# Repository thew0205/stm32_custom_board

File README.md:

# 🛠️ Custom STM32 Development Board

This project involves the design and fabrication of a **custom STM32 development board** based on the powerful **STM32F103C8T6** ARM Cortex-M3 microcontroller.

---

## 📷 Project Images

<div align="center">

</div>

---

## 🔧 Features

This custom board was designed from scratch to expose essential microcontroller capabilities while keeping the design compact and beginner-friendly.

- ✅ **Power Supply via USB**  
  – Provides both 5V power and USB 2.0 data communication

- 🔌 **Communication Interfaces (Breakouts)**  
  – UART  
  – I2C  

- ⚡ **GPIO Pin Breakouts**  
  – Full access to STM32 GPIOs  
  – Breadboard-friendly layout

---

## 📦 Tools and Technologies Used

- **KiCad** – Schematic & PCB design
- **STM32CubeProgrammer** – Flashing and testing
- **ST-Link v2** – SWD programming and debugging

---

## 🚀 Current Progress

- ✅ First prototype designed, routed, and fabricated
- ⚠️ Encountered soldering challenges during assembly
- 🔜 Second version planned with pre-soldered SMD components

---

## 🔬 What I Learned

- Hands-on STM32 microcontroller design
- USB data and power routing
- Communication protocol pinout handling
- Footprint selection and PCB layout best practices
- Hardware debugging and iterative prototyping

---

## 📁 Repository Contents

| File/Folder | Description |
|-------------|-------------|
| `stm32_custom_board.kicad_pcb` | PCB layout file |
| `stm32_custom_board.kicad_sch` | Circuit schematic |
| `629105150521 (rev1).stp`      | 3D model of the board |
| `image/`                       | PCB and prototype images |
| `.gitignore`                  | Git ignored files |
| `README.md`                   | Project documentation |

---

## 👤 Author

**Busoye Tolulope Matthew**  
Final Year Electrical & Electronic Engineering Student, University of Ibadan  
💡 Passionate about embedded systems, PCB design, and low-level programming.

- 🔗 [GitHub](https://github.com/thew0205)  
- 🔗 [LinkedIn](https://linkedin.com/in/busoye-tolulope-matthew)

---

## 📜 License

This project is open-source.  
Feel free to fork, build, and improve. Consider adding a license (e.g., MIT or CERN OHL) for clarity.

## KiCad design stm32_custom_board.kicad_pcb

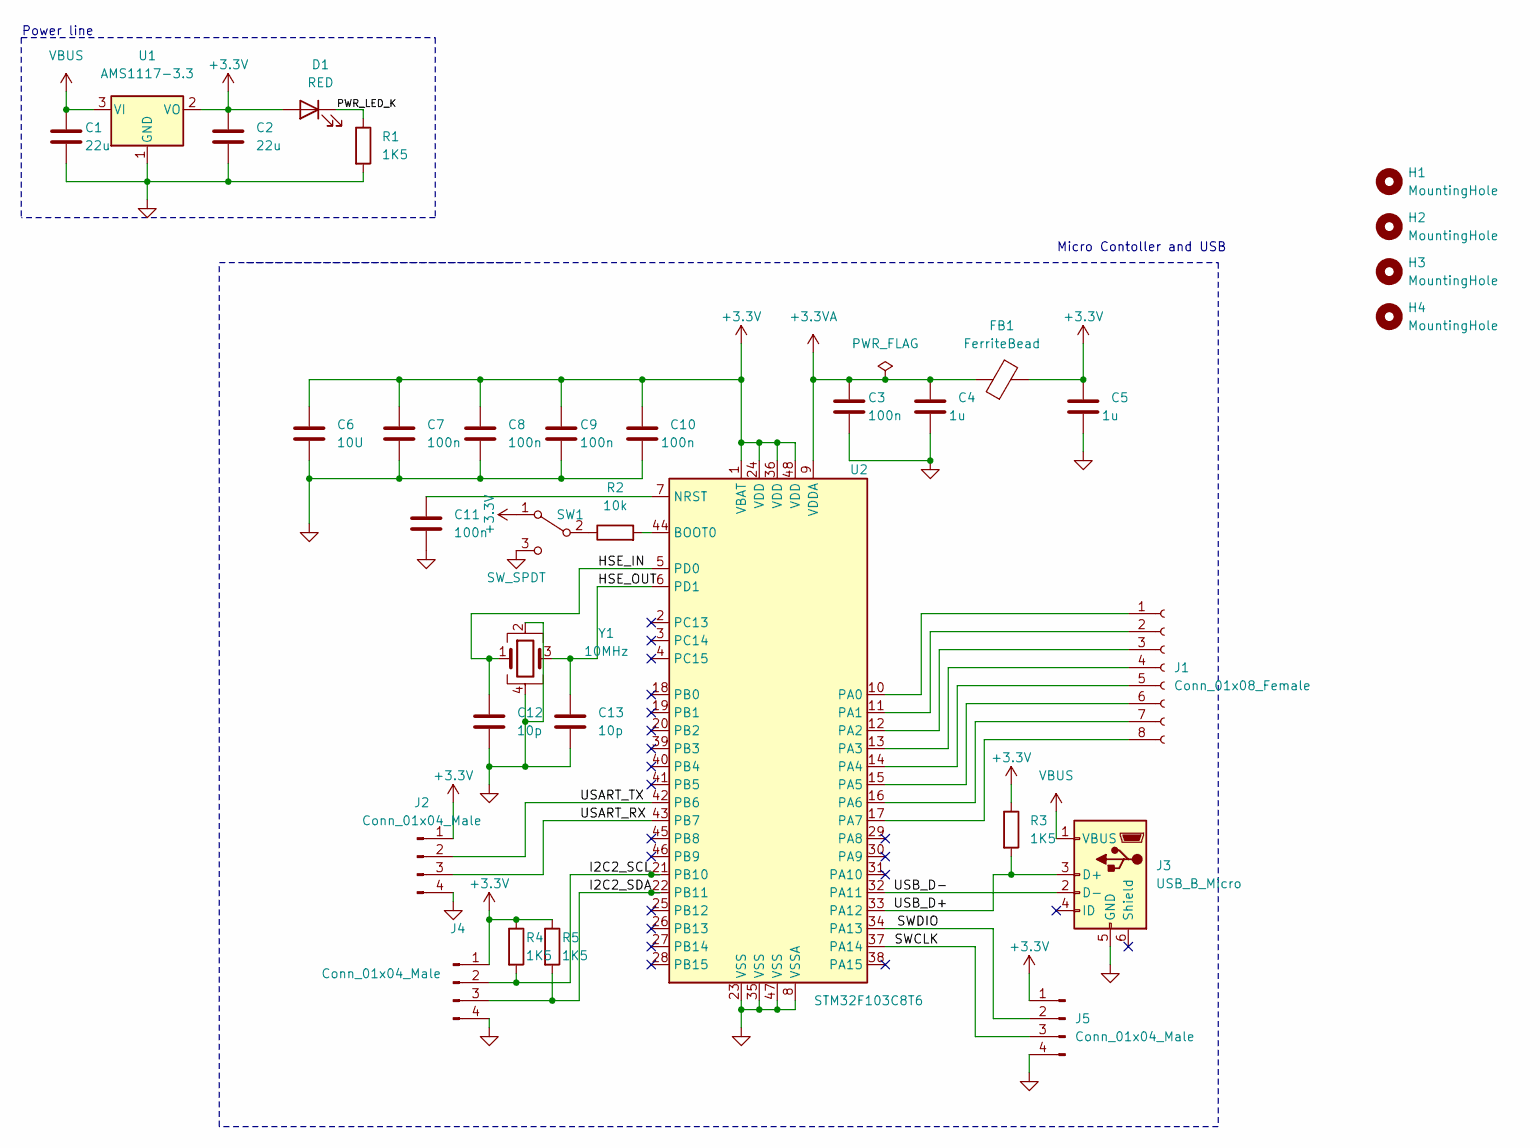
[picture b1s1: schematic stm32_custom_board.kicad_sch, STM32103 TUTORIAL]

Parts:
C1, C2: 22u; C_0805_2012Metric
C3, C7, C8, C9, C10, C11: 100n; C_0402_1005Metric
C4, C5: 1u; C_0402_1005Metric
C6: 10U; C_0603_1608Metric
C12, C13: 10p; C_0402_1005Metric
D1: RED; LED_0603_1608Metric
FB1: FerriteBead; L_0603_1608Metric
H1, H2, H3, H4: MountingHole; MountingHole_2.2mm_M2
J1: Conn_01x08_Female; PinSocket_1x08_P2.54mm_Vertical
J2, J4, J5: Conn_01x04_Male; PinHeader_1x04_P2.54mm_Vertical
J3: USB_B_Micro; USB_Micro-B_Wuerth_629105150521
R1, R3, R4, R5: 1K5; R_0402_1005Metric
R2: 10k; R_0402_1005Metric
SW1: SW_SPDT; SW_SPDT_PCM12
U1: AMS1117-3.3; SOT-223-3_TabPin2
U2: STM32F103C8T6; LQFP-48_7x7mm_P0.5mm
Y1: 10MHz; Crystal_SMD_3225-4Pin_3.2x2.5mm

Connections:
+3.3V: C2.1, C5.1, C6.1, C7.1, C8.1, C9.1, C10.1, D1.2 (A), FB1.2, J2.1, J4.1, J5.1, R3.1, R4.1, R5.1, SW1.1 (A), U1.2 (VO), U2.1 (VBAT), U2.24 (VDD), U2.36 (VDD), U2.48 (VDD)
+3.3VA: C3.1, C4.1, FB1.1, U2.9 (VDDA)
/HSE_IN: C12.1, U2.5 (PD0), Y1.1
/HSE_OUT: C13.1, U2.6 (PD1), Y1.3
/I2C2_SCL: J4.2, R4.2, U2.21 (PB10)
/I2C2_SDA: J4.3, R5.2, U2.22 (PB11)
/PWR_LED_K: D1.1 (K), R1.1
/SWCLK: J5.3, U2.37 (PA14)
/SWDIO: J5.2, U2.34 (PA13)
/USART_RX: J2.3, U2.43 (PB7)
/USART_TX: J2.2, U2.42 (PB6)
/USB_D+: J3.3 (D+), R3.2, U2.33 (PA12)
/USB_D-: J3.2 (D-), U2.32 (PA11)
GND: C1.2, C2.2, C3.2, C4.2, C5.2, C6.2, C7.2, C8.2, C9.2, C10.2, C11.2, C12.2, C13.2, J2.4, J3.5 (GND), J3.6 (Shield), J4.4, J5.4, R1.2, SW1.3 (C), U1.1 (GND), U2.8 (VSSA), U2.23 (VSS), U2.35 (VSS), U2.47 (VSS), Y1.2, Y1.4
unnamed: C11.1, U2.7 (NRST)
unnamed: J1.1, U2.10 (PA0)
unnamed: J1.2, U2.11 (PA1)
unnamed: J1.3, U2.12 (PA2)
unnamed: J1.4, U2.13 (PA3)
unnamed: J1.5, U2.14 (PA4)
unnamed: J1.6, U2.15 (PA5)
unnamed: J1.7, U2.16 (PA6)
unnamed: J1.8, U2.17 (PA7)
unnamed: R2.1, SW1.2 (B)
unnamed: R2.2, U2.44 (BOOT0)
VBUS: C1.1, J3.1 (VBUS), U1.3 (VI)

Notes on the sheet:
Micro Contoller and USB
Power line

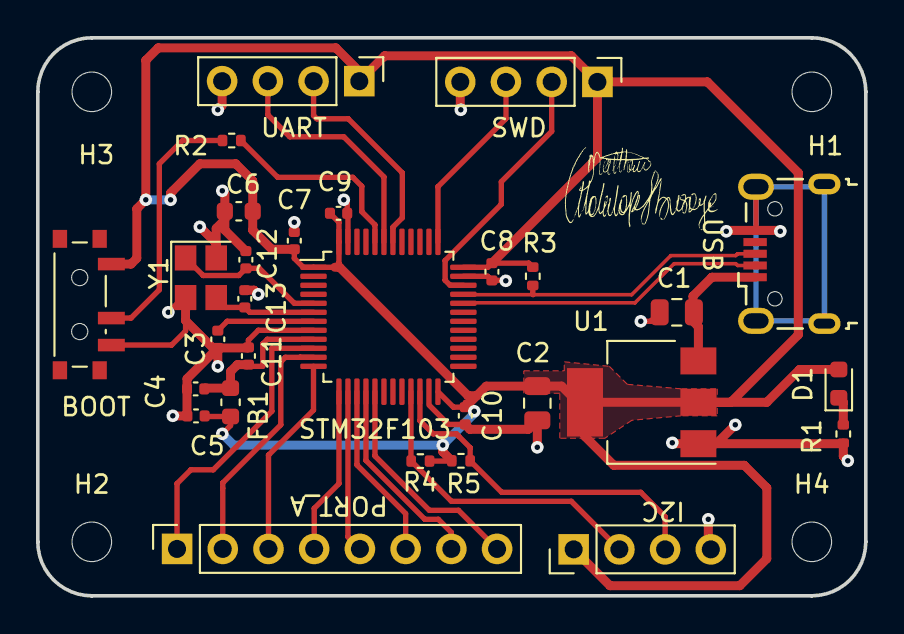
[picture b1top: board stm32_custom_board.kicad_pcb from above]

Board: 2 copper layers, 46.0 x 31.0 mm, 33 parts (0 on the bottom side), 26 nets.

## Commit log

2023-08-02 Adding frist prototype file
2025-06-06 added a README.md file
2025-06-06 added a gitignore file
2025-06-06 remove unnecessary traced files
2025-06-06 remove unnecessary traced filesg
2025-06-06 added project images
